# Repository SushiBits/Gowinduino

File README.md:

# Gowinduino

Gowinduino 是一款基于高云小蜜蜂 GW1NSR-4C 硬处理器 SoC FPGA 的试验开发板。

## 特性

GW1NSR-4C FPGA 有如下特性：

* 4608 个 LUT
* 3456 个寄存器
* 10 块 18kbit SRAM
* 256kbit 用户闪存
* 64Mbit PSRAM SiP
* 内置 Cortex-M3 硬 IP

本开发版有如下特性：

* 最高 12V 外部 DC 输入
* 3.3V I/O 电压
* Arduino Uno 脚位
* 集成 FT2232HL JTAG 和串口接口

## 授权许可

本作品是以[三条款 BSD 授权协议](LICENSE.md)授权的开源硬件。

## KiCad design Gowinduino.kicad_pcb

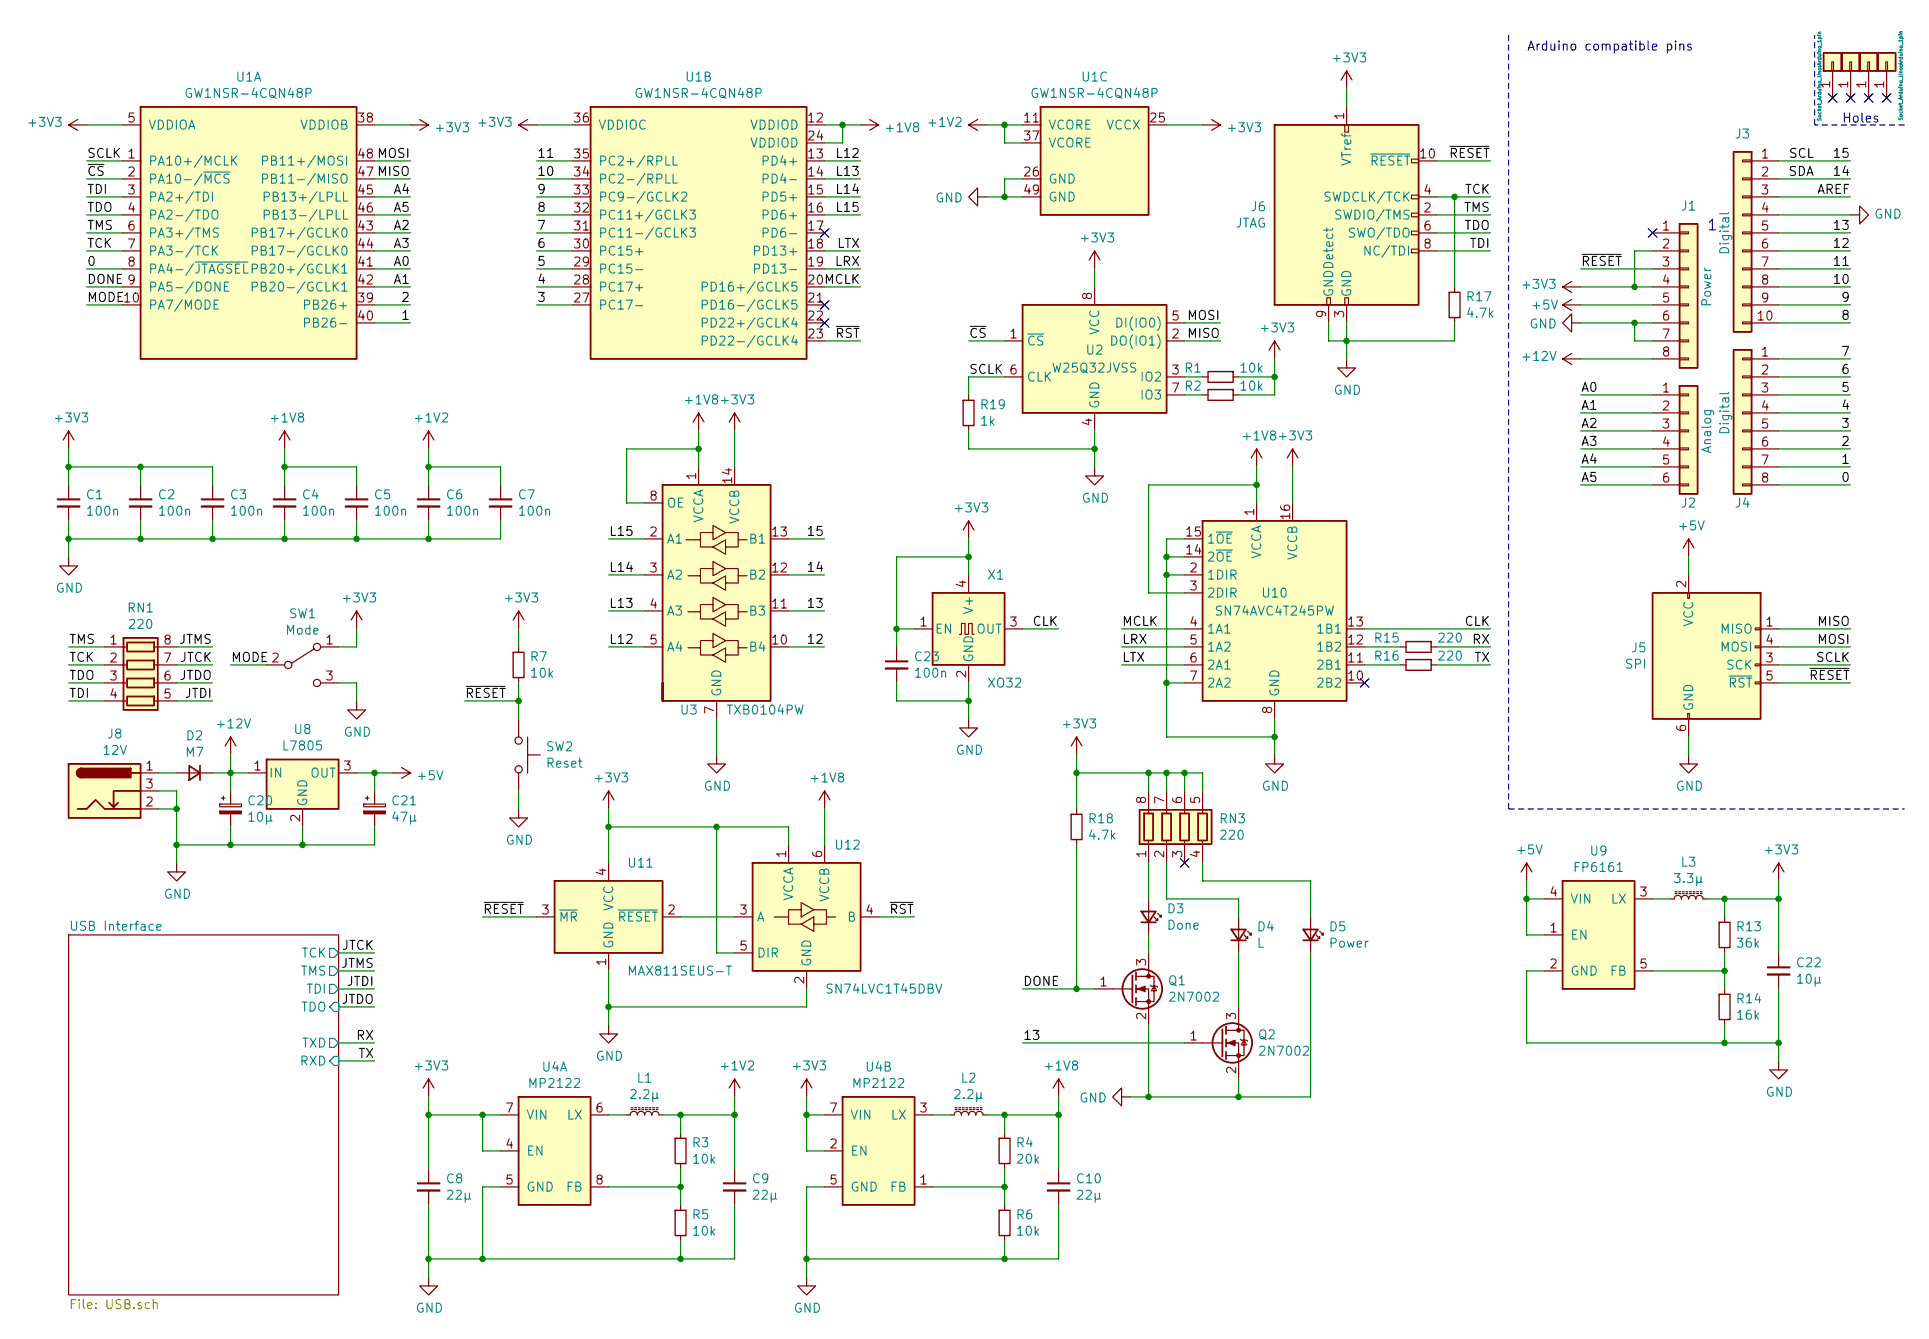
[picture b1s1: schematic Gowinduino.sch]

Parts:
C1, C2, C3, C4, C5, C6, C7, C23: 100n; C_0603_1608Metric_Pad1.08x0.95mm_HandSolder
C8, C9, C10: 22µ; C_0805_2012Metric_Pad1.18x1.45mm_HandSolder
C20: 10µ; CP_Elec_4x4.5
C21: 47µ; CP_Elec_4x4.5
C22: 10µ; C_0805_2012Metric_Pad1.18x1.45mm_HandSolder
D2: M7; D_SMA
D3: Done; LED_0805_2012Metric_Pad1.15x1.40mm_HandSolder
D4: L; LED_0805_2012Metric_Pad1.15x1.40mm_HandSolder
D5: Power; LED_0805_2012Metric_Pad1.15x1.40mm_HandSolder
J1: Power; PinSocket_1x08_P2.54mm_Vertical
J2: Analog; PinSocket_1x06_P2.54mm_Vertical
J3: Digital; PinSocket_1x10_P2.54mm_Vertical
J4: Digital; PinSocket_1x08_P2.54mm_Vertical
J5: SPI; PinHeader_2x03_P2.54mm_Vertical
J6: JTAG; PinHeader_2x05_P1.27mm_Vertical
J8: 12V; BarrelJack_Wuerth_6941xx301002
L1, L2: 2.2µ; L_0806_2014Metric_Pad1.15x1.60mm_HandSolder
L3: 3.3µ; L_0806_2014Metric_Pad1.15x1.60mm_HandSolder
PH1, PH2, PH3, PH4: CONN_01X01; Arduino_1pin
Q1, Q2: 2N7002; SOT-23
R1, R2, R3, R5, R6, R7: 10k; R_0603_1608Metric_Pad0.98x0.95mm_HandSolder
R4: 20k; R_0603_1608Metric_Pad0.98x0.95mm_HandSolder
R13: 36k; R_0603_1608Metric_Pad0.98x0.95mm_HandSolder
R14: 16k; R_0603_1608Metric_Pad0.98x0.95mm_HandSolder
R15, R16: 220; R_0603_1608Metric_Pad0.98x0.95mm_HandSolder
R17, R18: 4.7k; R_0603_1608Metric_Pad0.98x0.95mm_HandSolder
R19: 1k; R_0603_1608Metric_Pad0.98x0.95mm_HandSolder
RN1, RN3: 220; R_Array_Convex_4x0603
SW1: Mode; SW_SPDT_PCM12
SW2: Reset; SW_PUSH_6mm
U1: GW1NSR-4CQN48P; QFN-48-1EP_6x6mm_P0.4mm_EP4.2x4.2mm
U2: W25Q32JVSS; SOIC-8_5.23x5.23mm_P1.27mm
U3: TXB0104PW; TSSOP-14_4.4x5mm_P0.65mm
U4: MP2122; SOT-23-8
U8: L7805; TO-252-2
U9: FP6161; SOT-23-5
U10: SN74AVC4T245PW; TSSOP-16_4.4x5mm_P0.65mm
U11: MAX811SEUS-T; SOT-143
U12: SN74LVC1T45DBV; SOT-23-6
X1: XO32; Oscillator_SMD_EuroQuartz_XO32-4Pin_3.2x2.5mm

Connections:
+1V2: C6.1, C7.1, C9.1, L1.1, R3.1, U1.11 (VCORE), U1.37 (VCORE)
+1V8: C4.1, C5.1, C10.1, L2.1, R4.1, U1.12 (VDDIOD), U1.24 (VDDIOD), U3.1 (VCCA), U3.8 (OE), U10.1 (VCCA), U10.3 (2DIR), U12.6 (VCCB)
+3V3: C1.1, C2.1, C3.1, C8.1, C22.1, C23.1, J1.2, J1.4, J6.1 (VTref), L3.1, R1.1, R2.1, R7.1, R13.1, R18.1, RN3.5 (R4.2), RN3.6 (R3.2), RN3.7 (R2.2), RN3.8 (R1.2), SW1.1 (A), U1.5 (VDDIOA), U1.25 (VCCX), U1.36 (VDDIOC), U1.38 (VDDIOB), U2.8 (VCC), U3.14 (VCCB), U4.2 (EN), U4.4 (EN), U4.7 (VIN), U10.16 (VCCB), U11.4 (VCC), U12.1 (VCCA), U12.5 (DIR), X1.1 (EN), X1.4 (V+)
+5V: C21.1, J1.5, J5.2 (VCC), U8.3 (OUT), U9.1 (EN), U9.4 (VIN); also elsewhere on the board
+12V: C20.1, D2.1 (K), J1.8, U8.1 (IN)
/0: J4.8, U1.8 (PA4-/~JTAGSEL)
/1: J4.7, U1.40 (PB26-)
/2: J4.6, U1.39 (PB26+)
/3: J4.5, U1.27 (PC17-)
/4: J4.4, U1.28 (PC17+)
/5: J4.3, U1.29 (PC15-)
/6: J4.2, U1.30 (PC15+)
/7: J4.1, U1.31 (PC11-/GCLK3)
/8: J3.10, U1.32 (PC11+/GCLK3)
/9: J3.9, U1.33 (PC9-/GCLK2)
/10: J3.8, U1.34 (PC2-/RPLL)
/11: J3.7, U1.35 (PC2+/RPLL)
/12: J3.6, U3.10 (B4)
/13: J3.5, Q2.1 (G), U3.11 (B3)
/14: J3.2, U3.12 (B2)
/15: J3.1, U3.13 (B1)
/A0: J2.1, U1.41 (PB20+/GCLK1)
/A1: J2.2, U1.42 (PB20-/GCLK1)
/A2: J2.3, U1.43 (PB17+/GCLK0)
/A3: J2.4, U1.44 (PB17-/GCLK0)
/A4: J2.5, U1.45 (PB13+/LPLL)
/A5: J2.6, U1.46 (PB13-/LPLL)
/CLK: U10.13 (1B1), X1.3 (OUT)
/DONE: Q1.1 (G), R18.2, U1.9 (PA5-/DONE)
/JTCK: RN1.7 (R2.2); also elsewhere on the board
/JTDI: RN1.5 (R4.2); also elsewhere on the board
/JTDO: RN1.6 (R3.2); also elsewhere on the board
/JTMS: RN1.8 (R1.2); also elsewhere on the board
/L12: U1.13 (PD4+), U3.5 (A4)
/L13: U1.14 (PD4-), U3.4 (A3)
/L14: U1.15 (PD5+), U3.3 (A2)
/L15: U1.16 (PD6+), U3.2 (A1)
/LRX: U1.19 (PD13-), U10.5 (1A2)
/LTX: U1.18 (PD13+), U10.6 (2A1)
/MCLK: U1.20 (PD16+/GCLK5), U10.4 (1A1)
/MISO: J5.1 (MISO), U1.47 (PB11-/MISO), U2.2 (DO(IO1))
/MODE: SW1.2 (B), U1.10 (PA7/MODE)
/MOSI: J5.4 (MOSI), U1.48 (PB11+/MOSI), U2.5 (DI(IO0))
/RX: R15.1; also elsewhere on the board
/SCLK: J5.3 (SCK), R19.1, U1.1 (PA10+/MCLK), U2.6 (CLK)
/TCK: J6.4 (SWDCLK/TCK), R17.1, RN1.2 (R2.1), U1.7 (PA3-/TCK)
/TDI: J6.8 (NC/TDI), RN1.4 (R4.1), U1.3 (PA2+/TDI)
/TDO: J6.6 (SWO/TDO), RN1.3 (R3.1), U1.4 (PA2-/TDO)
/TMS: J6.2 (SWDIO/TMS), RN1.1 (R1.1), U1.6 (PA3+/TMS)
/TX: R16.1; also elsewhere on the board
/~CS: U1.2 (PA10-/~MCS), U2.1 (~CS)
/~RESET: J1.3, J5.5 (~RST), J6.10 (~RESET~), R7.2, SW2.1, U11.3 (~MR)
/~RST: U1.23 (PD22-/GCLK4), U12.4 (B)
GND: C1.2, C2.2, C3.2, C4.2, C5.2, C6.2, C7.2, C8.2, C9.2, C10.2, C20.2, C21.2, C22.2, C23.2, D5.1 (K), J1.6, J1.7, J3.4, J5.6 (GND), J6.3 (GND), J6.5 (GND), J6.9 (GNDDetect), J8.2, J8.3, Q1.2 (S), Q2.2 (S), R5.2, R6.2, R14.2, R17.2, R19.2, SW1.3 (C), SW2.2, U1.26 (GND), U1.49 (GND), U2.4 (GND), U3.7 (GND), U4.5 (GND), U8.2 (GND), U9.2 (GND), U10.2 (1DIR), U10.7 (2A2), U10.8 (GND), U10.9 (GND), U10.14 (2~OE), U10.15 (1~OE), U11.1 (GND), U12.2 (GND), X1.2 (GND); also elsewhere on the board
unnamed: D2.2 (A), J8.1
unnamed: D3.1 (K), Q1.3 (D)
unnamed: D3.2 (A), RN3.1 (R1.1)
unnamed: D4.1 (K), Q2.3 (D)
unnamed: D4.2 (A), RN3.2 (R2.1)
unnamed: D5.2 (A), RN3.4 (R4.1)
unnamed: L1.2, U4.6 (LX)
unnamed: L2.2, U4.3 (LX)
unnamed: L3.2, U9.3 (LX)
unnamed: R1.2, U2.3 (IO2)
unnamed: R2.2, U2.7 (IO3)
unnamed: R3.2, R5.1, U4.8 (FB)
unnamed: R4.2, R6.1, U4.1 (FB)
unnamed: R13.2, R14.1, U9.5 (FB)
unnamed: R15.2, U10.12 (1B2)
unnamed: R16.2, U10.11 (2B1)
unnamed: U11.2 (~RESET), U12.3 (A)

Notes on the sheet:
Holes
Arduino compatible pins

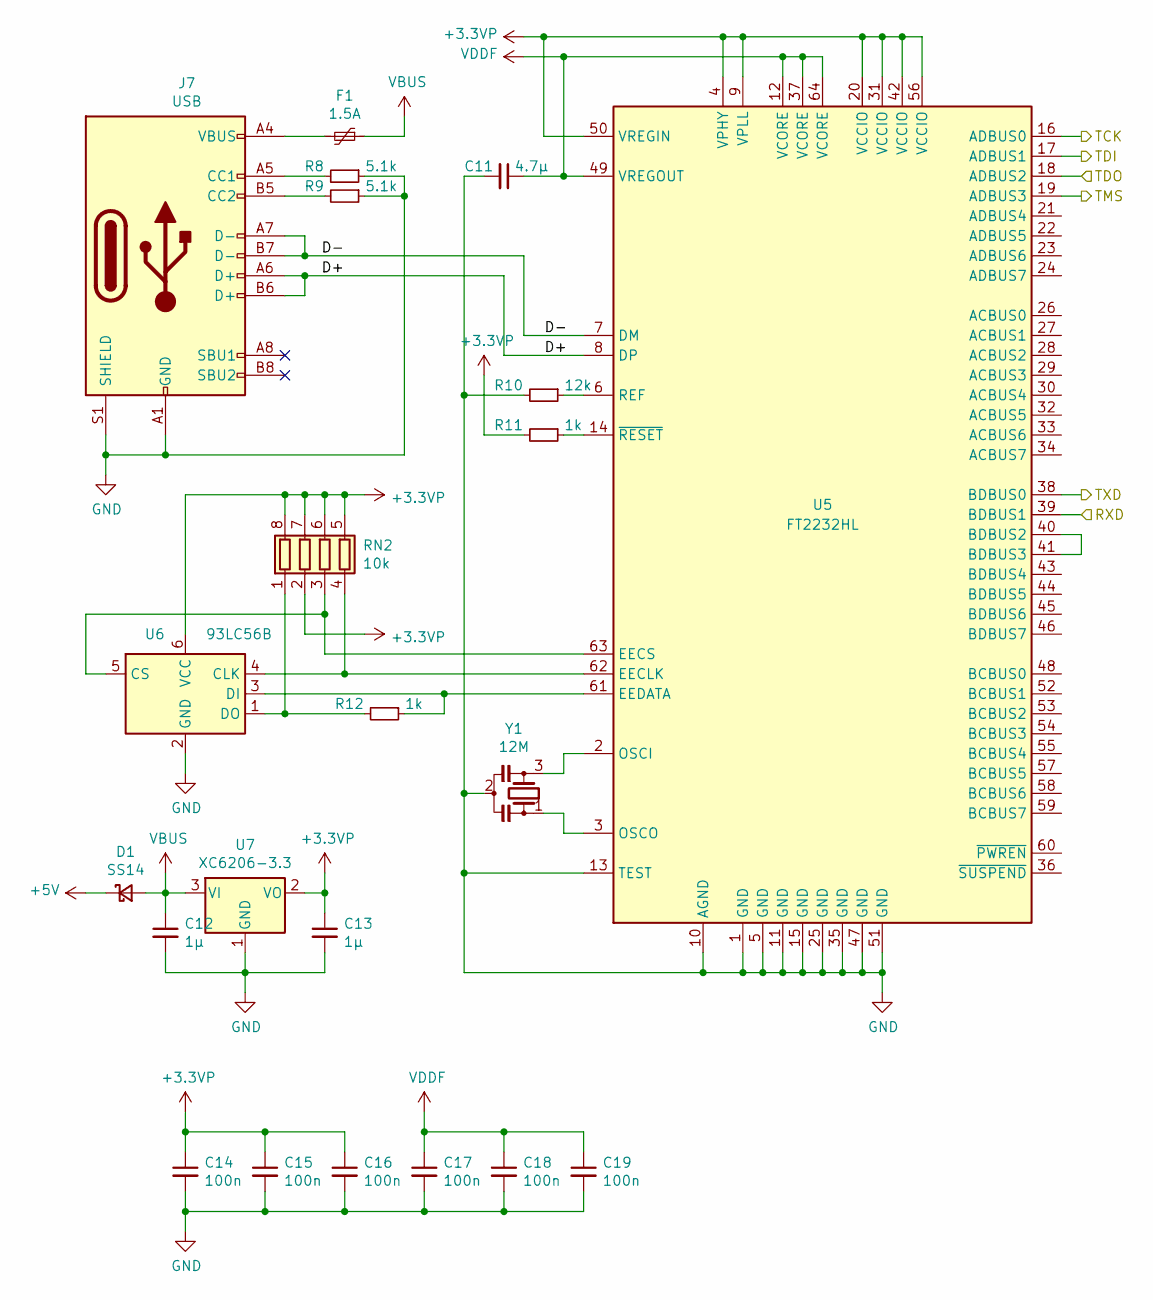
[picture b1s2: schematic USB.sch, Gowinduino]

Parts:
C11: 4.7µ; C_0603_1608Metric_Pad1.08x0.95mm_HandSolder
C12, C13: 1µ; C_0603_1608Metric_Pad1.08x0.95mm_HandSolder
C14, C15, C16, C17, C18, C19: 100n; C_0603_1608Metric_Pad1.08x0.95mm_HandSolder
D1: SS14; D_SMA
F1: 1.5A; Fuse_1812_4532Metric_Pad1.30x3.40mm_HandSolder
J7: USB; USB_C_Receptacle_HRO_TYPE-C-31-M-12
R8, R9: 5.1k; R_0603_1608Metric_Pad0.98x0.95mm_HandSolder
R10: 12k; R_0603_1608Metric_Pad0.98x0.95mm_HandSolder
R11, R12: 1k; R_0603_1608Metric_Pad0.98x0.95mm_HandSolder
RN2: 10k; R_Array_Convex_4x0603
U5: FT2232HL; LQFP-64_10x10mm_P0.5mm
U6: 93LC56B; SOT-23-6
U7: XC6206-3.3; SOT-23
Y1: 12M; Resonator_SMD_muRata_CSTxExxV-3Pin_3.0x1.1mm

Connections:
+3.3VP: C13.1, C14.1, C15.1, C16.1, R11.2, RN2.2 (R2.1), RN2.5 (R4.2), RN2.6 (R3.2), RN2.7 (R2.2), RN2.8 (R1.2), U5.4 (VPHY), U5.9 (VPLL), U5.20 (VCCIO), U5.31 (VCCIO), U5.42 (VCCIO), U5.50 (VREGIN), U5.56 (VCCIO), U6.6 (VCC), U7.2 (VO)
+5V: D1.1 (K); also elsewhere on the board
/JTCK: U5.16 (ADBUS0); also elsewhere on the board
/JTDI: U5.17 (ADBUS1); also elsewhere on the board
/JTDO: U5.18 (ADBUS2); also elsewhere on the board
/JTMS: U5.19 (ADBUS3); also elsewhere on the board
/RX: U5.38 (BDBUS0); also elsewhere on the board
/TX: U5.39 (BDBUS1); also elsewhere on the board
/USB Interface/D+: J7.A6 (D+), J7.B6 (D+), U5.8 (DP)
/USB Interface/D-: J7.A7 (D-), J7.B7 (D-), U5.7 (DM)
GND: C11.2, C12.2, C13.2, C14.2, C15.2, C16.2, C17.2, C18.2, C19.2, J7.A1 (GND), J7.A12 (GND), J7.B1 (GND), J7.B12 (GND), J7.S1 (SHIELD), R8.1, R9.1, R10.2, U5.1 (GND), U5.5 (GND), U5.10 (AGND), U5.11 (GND), U5.13 (TEST), U5.15 (GND), U5.25 (GND), U5.35 (GND), U5.47 (GND), U5.51 (GND), U6.2 (GND), U7.1 (GND), Y1.2; also elsewhere on the board
unnamed: F1.2, J7.A4 (VBUS), J7.A9 (VBUS), J7.B4 (VBUS), J7.B9 (VBUS)
unnamed: J7.A5 (CC1), R8.2
unnamed: J7.B5 (CC2), R9.2
unnamed: R10.1, U5.6 (REF)
unnamed: R11.1, U5.14 (~RESET)
unnamed: R12.1, U5.61 (EEDATA), U6.3 (DI)
unnamed: R12.2, RN2.1 (R1.1), U6.1 (DO)
unnamed: RN2.3 (R3.1), U5.63 (EECS), U6.5 (CS)
unnamed: RN2.4 (R4.1), U5.62 (EECLK), U6.4 (CLK)
unnamed: U5.2 (OSCI), Y1.3
unnamed: U5.3 (OSCO), Y1.1
unnamed: U5.40 (BDBUS2), U5.41 (BDBUS3)
VBUS: C12.1, D1.2 (A), F1.1, U7.3 (VI)
VDDF: C11.1, C17.1, C18.1, C19.1, U5.12 (VCORE), U5.37 (VCORE), U5.49 (VREGOUT), U5.64 (VCORE)

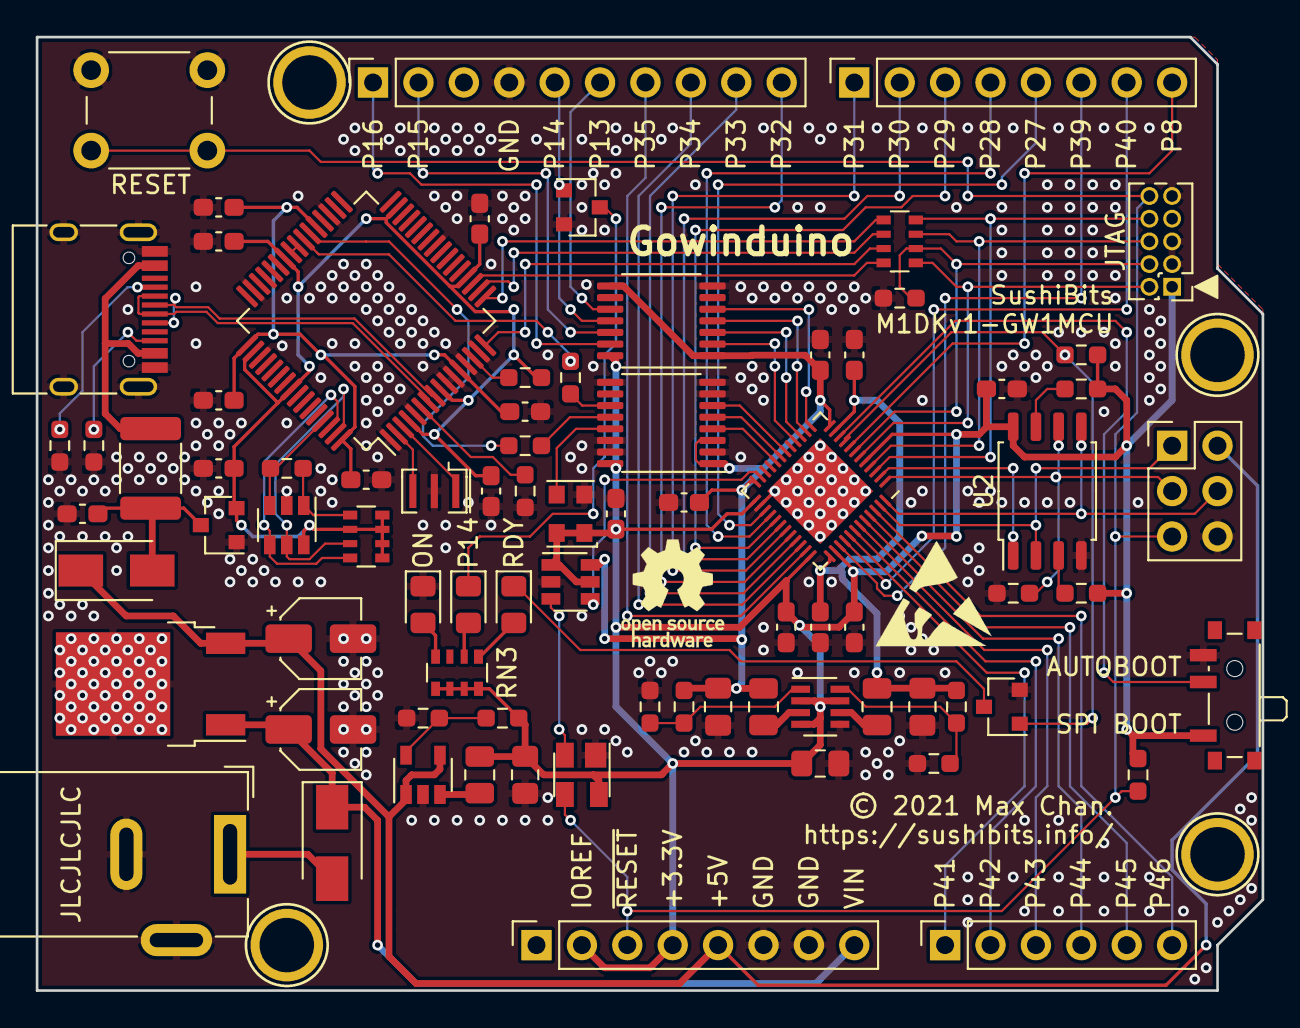
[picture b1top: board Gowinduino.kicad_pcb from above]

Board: 2 copper layers, 68.6 x 53.3 mm, 84 parts (0 on the bottom side), 88 nets.

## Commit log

2021-04-16 Base KiCad Arduino Uno project
2021-04-16 Schematics: Introduced Arduino IO pins, FPGA and SPI Flash.
2021-04-16 PCB: Introduced Arduino pins.
2021-04-16 PCB: Introduced FPGA and SPI Flash
2021-04-16 Introduced JLCPCB DRC rules and GND fills
2021-04-16 PCB: Locating SPI Flash resistors.
2021-04-16 PCB: Hooking up the JTAG port.
2021-04-17 PCB: Hookup all 3.3V IO pins
2021-04-17 Implemented the 1.8V conversion out
2021-04-18 PCB: Wiring up all GPIO pins
2021-04-18 Implemented: USB and 12V VIN
2021-04-18 Via stitching at 5V regulator
2021-04-18 More via stitching at 5V regulator
2021-04-18 Various touchups around the PCB.
2021-04-18 Schematics: LEDs
2021-04-18 PCB: Layout done, now stitching vias
2021-04-18 FInals: front-side silkscreens
2021-04-18 Name on the drawings
2021-04-18 OSHW and ESD symbols

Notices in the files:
Gowinduino.kicad_pcb:
© 2021 Max Chan.
Gowinduino.sch:
© 2021 Max Chan. https://sushibits.info
